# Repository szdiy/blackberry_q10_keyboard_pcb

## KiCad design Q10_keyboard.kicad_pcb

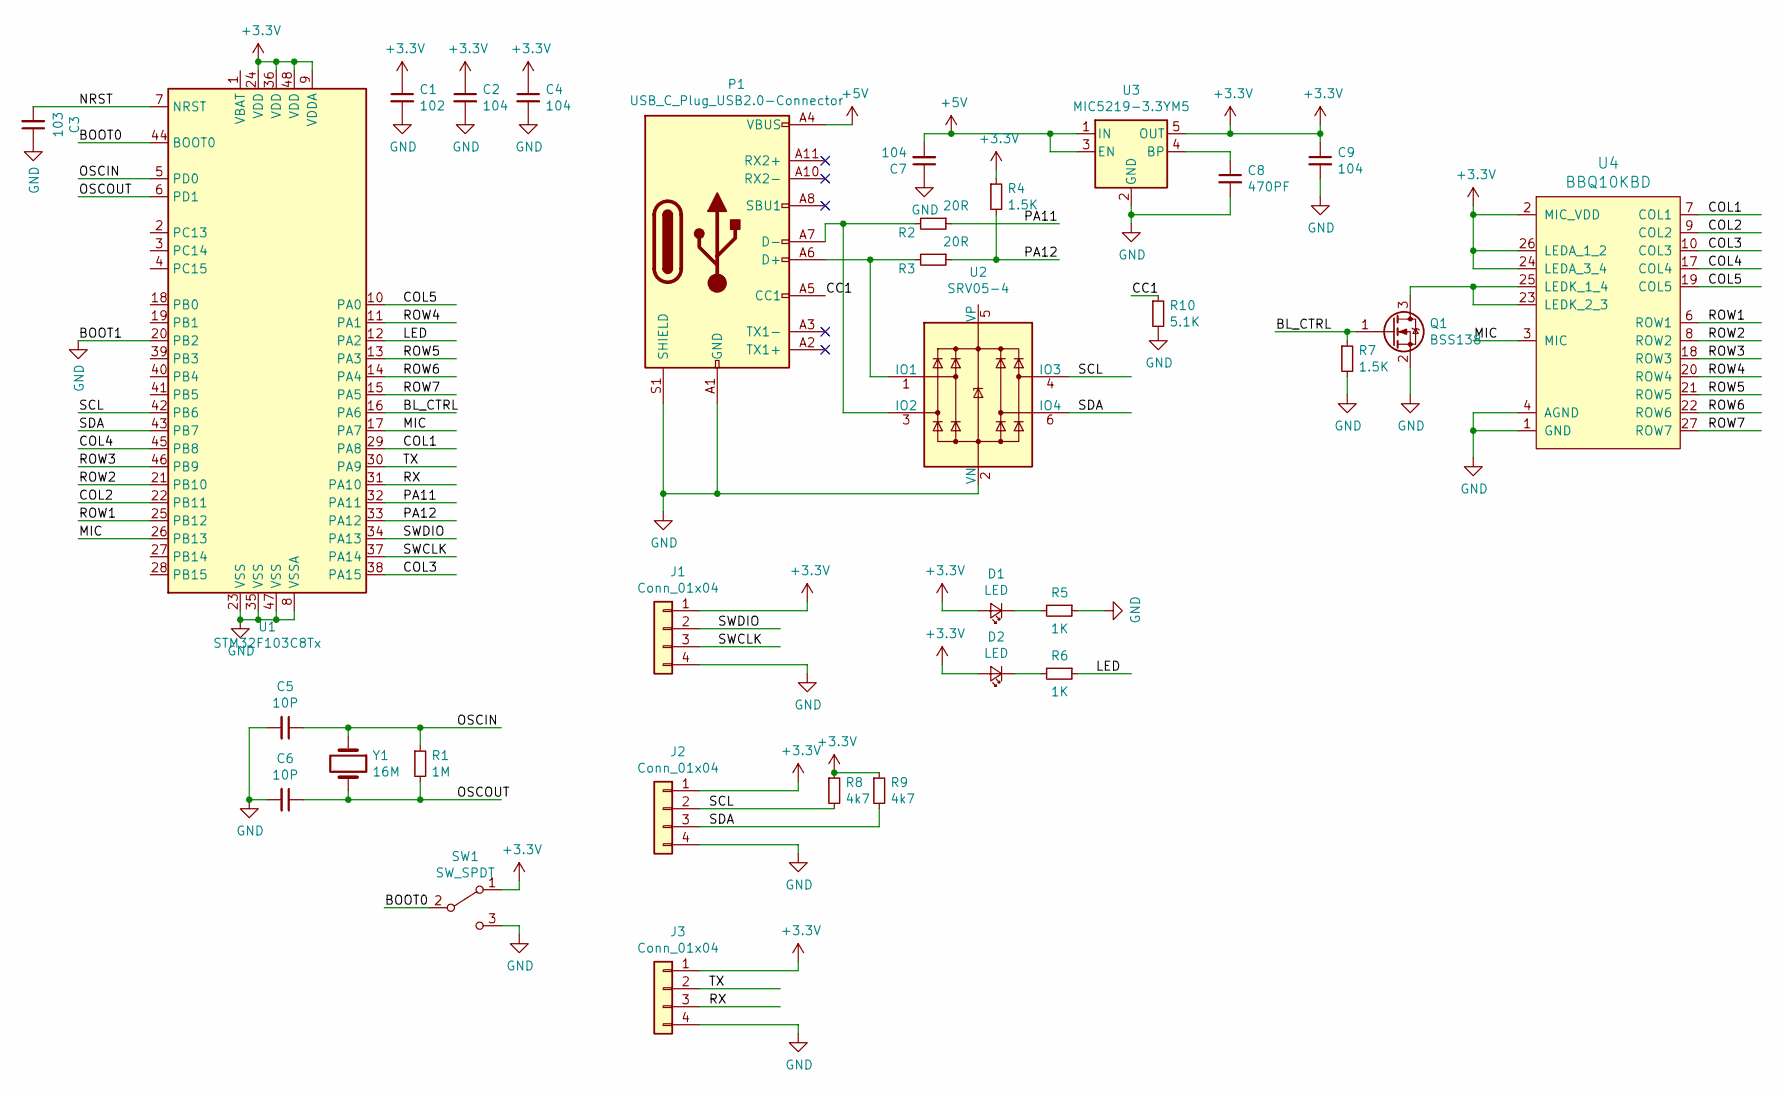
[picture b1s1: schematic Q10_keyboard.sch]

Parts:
C1: 102; C_0603_1608Metric_Pad1.05x0.95mm_HandSolder
C2, C4, C7, C9: 104; C_0603_1608Metric_Pad1.05x0.95mm_HandSolder
C3: 103; C_0603_1608Metric_Pad1.05x0.95mm_HandSolder
C5, C6: 10P; C_0603_1608Metric_Pad1.05x0.95mm_HandSolder
C8: 470PF; C_0603_1608Metric_Pad1.05x0.95mm_HandSolder
D1, D2: LED; LED_0603_1608Metric_Pad1.05x0.95mm_HandSolder
J1, J2, J3: Conn_01x04; PinHeader_1x04_P2.54mm_Vertical
P1: USB_C_Plug_USB2.0-Connector; USB_C_Receptacle_HRO_TYPE-C-31-M-12
Q1: BSS138; SOT-23
R1: 1M; R_0603_1608Metric_Pad1.05x0.95mm_HandSolder
R2, R3: 20R; R_0603_1608Metric_Pad1.05x0.95mm_HandSolder
R4, R7: 1.5K; R_0603_1608Metric_Pad1.05x0.95mm_HandSolder
R5, R6: 1K; R_0603_1608Metric_Pad1.05x0.95mm_HandSolder
R8, R9: 4k7; R_0603_1608Metric_Pad1.05x0.95mm_HandSolder
R10: 5.1K; R_0603_1608Metric_Pad1.05x0.95mm_HandSolder
SW1: SW_SPDT; SW_SPDT_PCM12
U1: STM32F103C8Tx; LQFP-48_7x7mm_P0.5mm
U2: SRV05-4; SOT-23-6
U3: MIC5219-3.3YM5; SOT-23-5
U4: BBQ10KBD; BM14B(0.8)-24DS-0.4V(53)
Y1: 16M; Crystal_SMD_3225-4Pin_3.2x2.5mm_HandSoldering

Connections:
+3V3: C1.1, C2.1, C4.1, C9.1, D1.2 (A), D2.2 (A), J1.1, J2.1, J3.1, R4.1, R8.1, R9.1, SW1.1 (A), U1.9 (VDDA), U1.24 (VDD), U1.36 (VDD), U1.48 (VDD), U3.5 (OUT), U4.2 (MIC_VDD), U4.24 (LEDA_3_4), U4.26 (LEDA_1_2)
+5V: C7.2, P1.A4 (VBUS), P1.A9 (VBUS), P1.B4 (VBUS), P1.B9 (VBUS), U3.1 (IN), U3.3 (EN)
/BL_CTRL: Q1.1 (G), R7.1, U1.16 (PA6)
/BOOT0: SW1.2 (B), U1.44 (BOOT0)
/CC1: P1.A5 (CC1), R10.1
/COL1: U1.29 (PA8), U4.7 (COL1)
/COL2: U1.22 (PB11), U4.9 (COL2)
/COL3: U1.38 (PA15), U4.10 (COL3)
/COL4: U1.45 (PB8), U4.17 (COL4)
/COL5: U1.10 (PA0), U4.19 (COL5)
/LED: R6.1, U1.12 (PA2)
/MIC: U1.17 (PA7), U1.26 (PB13), U4.3 (MIC)
/NRST: C3.2, U1.7 (NRST)
/OSCIN: C5.1, R1.1, U1.5 (PD0), Y1.1
/OSCOUT: C6.1, R1.2, U1.6 (PD1), Y1.2
/PA11: R2.1, U1.32 (PA11)
/PA12: R3.1, R4.2, U1.33 (PA12)
/ROW1: U1.25 (PB12), U4.6 (ROW1)
/ROW2: U1.21 (PB10), U4.8 (ROW2)
/ROW3: U1.46 (PB9), U4.18 (ROW3)
/ROW4: U1.11 (PA1), U4.20 (ROW4)
/ROW5: U1.13 (PA3), U4.21 (ROW5)
/ROW6: U1.14 (PA4), U4.22 (ROW6)
/ROW7: U1.15 (PA5), U4.27 (ROW7)
/RX: J3.3, U1.31 (PA10)
/SCL: J2.2, R8.2, U1.42 (PB6), U2.4 (IO3)
/SDA: J2.3, R9.2, U1.43 (PB7), U2.6 (IO4)
/SWCLK: J1.3, U1.37 (PA14)
/SWDIO: J1.2, U1.34 (PA13)
/TX: J3.2, U1.30 (PA9)
GND: C1.2, C2.2, C3.1, C4.2, C5.2, C6.2, C7.1, C8.2, C9.2, J1.4, J2.4, J3.4, P1.A1 (GND), P1.A12 (GND), P1.B1 (GND), P1.B12 (GND), P1.S1 (SHIELD), Q1.2 (S), R5.1, R7.2, R10.2, SW1.3 (C), U1.8 (VSSA), U1.20 (PB2), U1.23 (VSS), U1.35 (VSS), U1.47 (VSS), U2.2 (VN), U3.2 (GND), U4.1 (GND), U4.4 (AGND), U4.5 (GND), U4.11 (GND), U4.12 (GND), U4.13 (GND), U4.14 (GND), U4.15 (GND), U4.16 (GND), U4.28 (GND)
unnamed: C8.1, U3.4 (BP)
unnamed: D1.1 (K), R5.2
unnamed: D2.1 (K), R6.2
unnamed: P1.A6 (D+), R3.2, U2.1 (IO1)
unnamed: P1.A7 (D-), R2.2, U2.3 (IO2)
unnamed: Q1.3 (D), U4.23 (LEDK_2_3), U4.25 (LEDK_1_4)

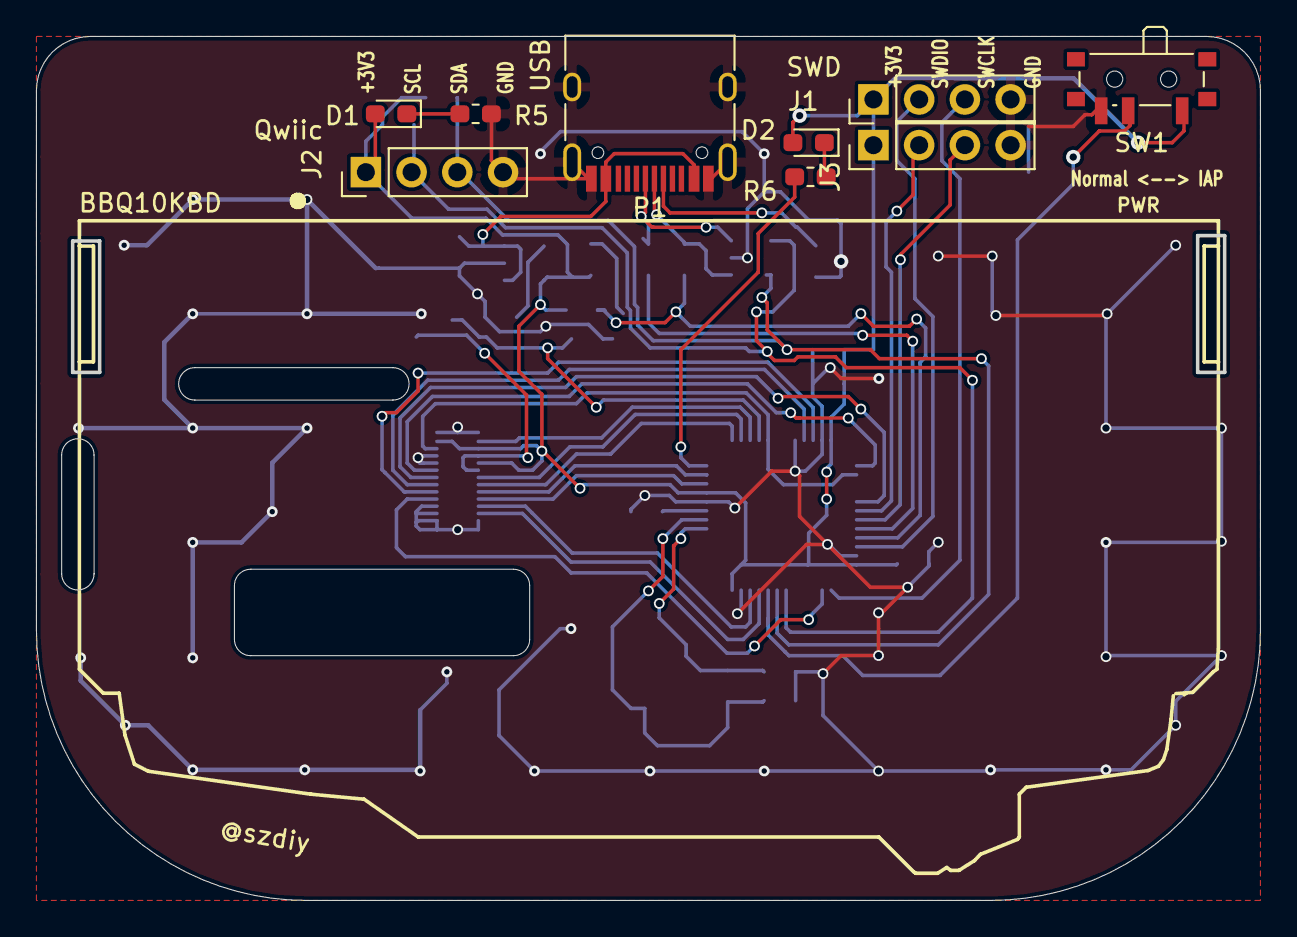
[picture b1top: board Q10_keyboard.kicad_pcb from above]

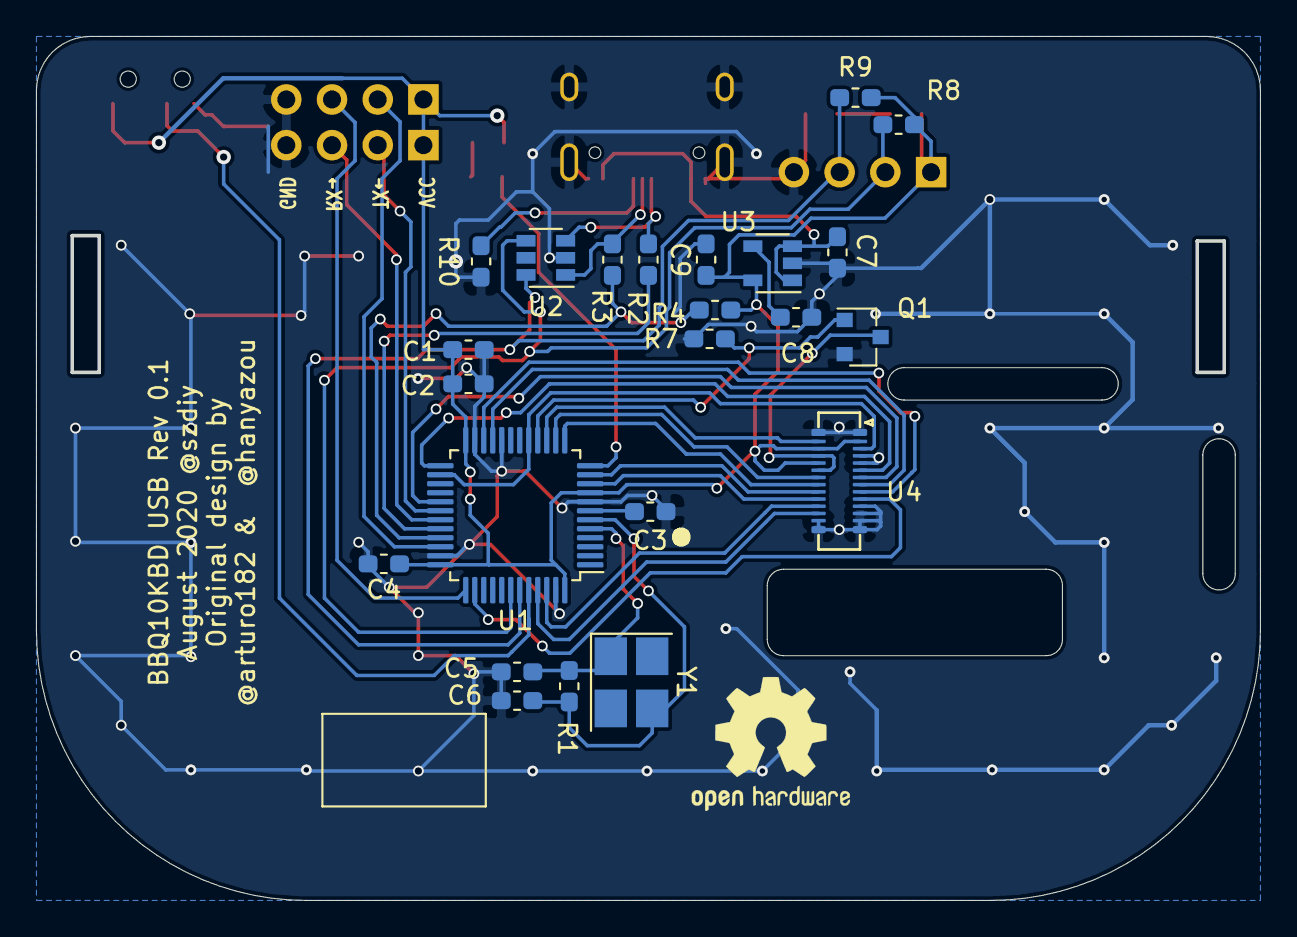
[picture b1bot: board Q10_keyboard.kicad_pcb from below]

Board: 2 copper layers, 68.0 x 48.0 mm, 32 parts (23 on the bottom side), 37 nets.

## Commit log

2020-10-12 Fixed some bugs after PCB manufacturing
2020-10-13 Add 5.1k pull-down on USB Type-C CC1 pin
